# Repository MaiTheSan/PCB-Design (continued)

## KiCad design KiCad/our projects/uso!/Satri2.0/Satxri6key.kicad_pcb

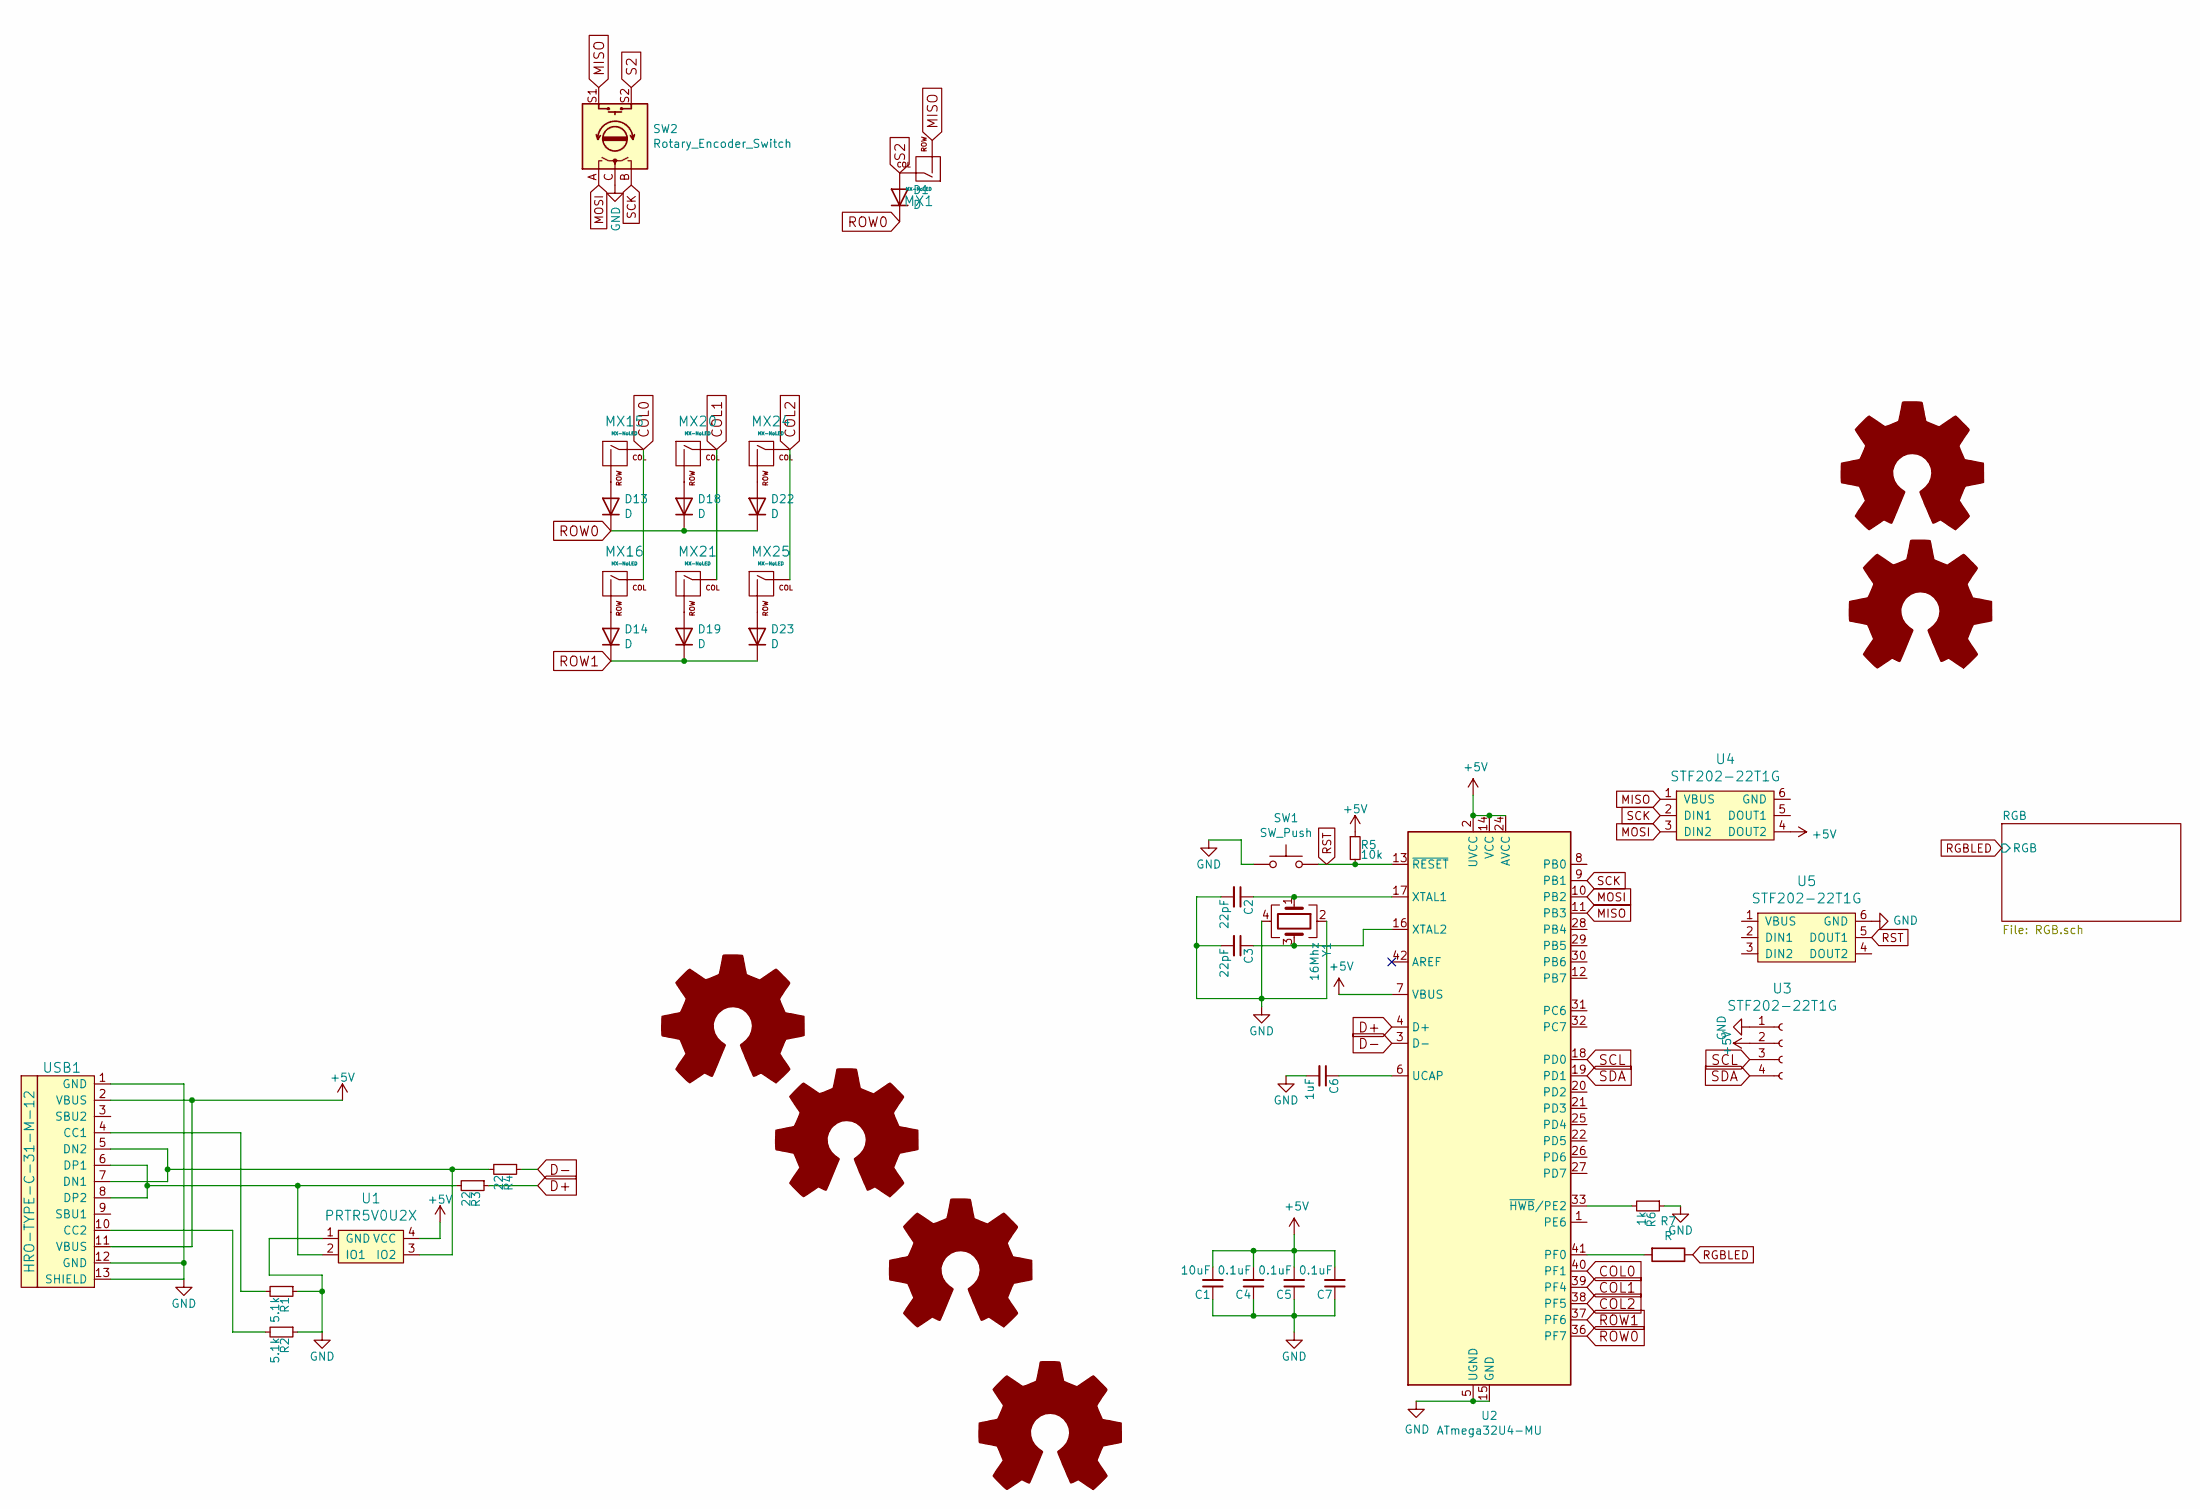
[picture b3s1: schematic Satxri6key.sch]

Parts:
C1: 10uF; C_0603
C2, C3: 22pF; C_0603
C4, C5, C7: 0.1uF; C_0603
C6: 1uF; C_0603
D1, D13, D14, D18, D19, D22, D23: D; D_SOD-123
LOGO1: Logo_Open_Hardware_Large; sanpjxlogo-PCB-type
LOGO2, LOGO3, LOGO4, LOGO5: Logo_Open_Hardware_Large; MountingHole_2.2mm_M2_DIN965_Pad
LOGO6: Logo_Open_Hardware_Large; satxrilogo
MX1, MX15, MX16, MX20, MX21, MX24, MX25: MX-NoLED; MXOnly-1U-Hotswap
R1, R2: 5.1k; R_0805
R3, R4: 22; R_0805
R5: 10k; R_0805
R6: 1k; R_0805
R7: R; R_0805
SW1: SW_Push; SKQG-1155865
SW2: Rotary_Encoder_Switch; RotaryEncoder_Alps_EC11E-Switch_Vertical_H20mm_Center
U1: PRTR5V0U2X; SOT143B
U2: ATmega32U4-MU; QFN-44-1EP_7x7mm_P0.5mm_EP5.2x5.2mm_ThermalVias
U3: STF202-22T1G; 0.91_SSD1306_OLED
U4, U5: STF202-22T1G; Reset_Pretty
USB1: HRO-TYPE-C-31-M-12; HRO-TYPE-C-31-M-12-Assembly
Y1: 16Mhz; Crystal_SMD_3225-4Pin_3.2x2.5mm

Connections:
+5V: C1.2, C4.2, C5.2, C7.2, R5.1, U1.4 (VCC), U2.2 (UVCC), U2.7 (VBUS), U2.14 (VCC), U2.24 (AVCC), U2.34 (VCC), U2.44 (AVCC), U3.2, U4.4 (DOUT2), USB1.2 (VBUS), USB1.11 (VBUS); also elsewhere on the board
COL0: MX15.1 (COL), MX16.1 (COL), U2.40 (PF1)
COL1: MX20.1 (COL), MX21.1 (COL), U2.39 (PF4)
COL2: MX24.1 (COL), MX25.1 (COL), U2.38 (PF5)
D+: R3.1, U2.4 (D+)
D-: R4.1, U2.3 (D-)
GND: C1.1, C2.2, C3.2, C4.1, C5.1, C6.2, C7.1, R1.1, R2.1, R6.1, SW1.1, SW2.C, U1.1 (GND), U2.5 (UGND), U2.15 (GND), U2.23 (GND), U2.35 (GND), U2.43 (GND), U2.45 (GND), U3.1, U5.6 (GND), USB1.1 (GND), USB1.12 (GND), USB1.13 (SHIELD), Y1.2, Y1.4; also elsewhere on the board
MISO: MX1.2 (ROW), SW2.S1, U2.11 (PB3), U4.1 (VBUS)
MOSI: SW2.A, U2.10 (PB2), U4.3 (DIN2)
unnamed: C2.1, U2.17 (XTAL1), Y1.1
unnamed: C3.1, U2.16 (XTAL2), Y1.3
unnamed: C6.1, U2.6 (UCAP)
unnamed: D13.2 (A), MX15.2 (ROW)
unnamed: D14.2 (A), MX16.2 (ROW)
unnamed: D18.2 (A), MX20.2 (ROW)
unnamed: D19.2 (A), MX21.2 (ROW)
unnamed: D22.2 (A), MX24.2 (ROW)
unnamed: D23.2 (A), MX25.2 (ROW)
unnamed: R1.2, USB1.4 (CC1)
unnamed: R2.2, USB1.10 (CC2)
unnamed: R3.2, U1.2 (IO1), USB1.6 (DP1), USB1.8 (DP2)
unnamed: R4.2, U1.3 (IO2), USB1.5 (DN2), USB1.7 (DN1)
unnamed: R6.2, U2.33 (~HWB~/PE2)
unnamed: R7.2, U2.41 (PF0)
RGBLED: R7.1; also elsewhere on the board
ROW0: D1.1 (K), D13.1 (K), D18.1 (K), D22.1 (K), U2.36 (PF7)
ROW1: D14.1 (K), D19.1 (K), D23.1 (K), U2.37 (PF6)
RST: R5.2, SW1.2, U2.13 (~RESET), U5.5 (DOUT1)
S2: D1.2 (A), MX1.1 (COL), SW2.S2
SCK: SW2.B, U2.9 (PB1), U4.2 (DIN1)
SCL: U2.18 (PD0), U3.3
SDA: U2.19 (PD1), U3.4

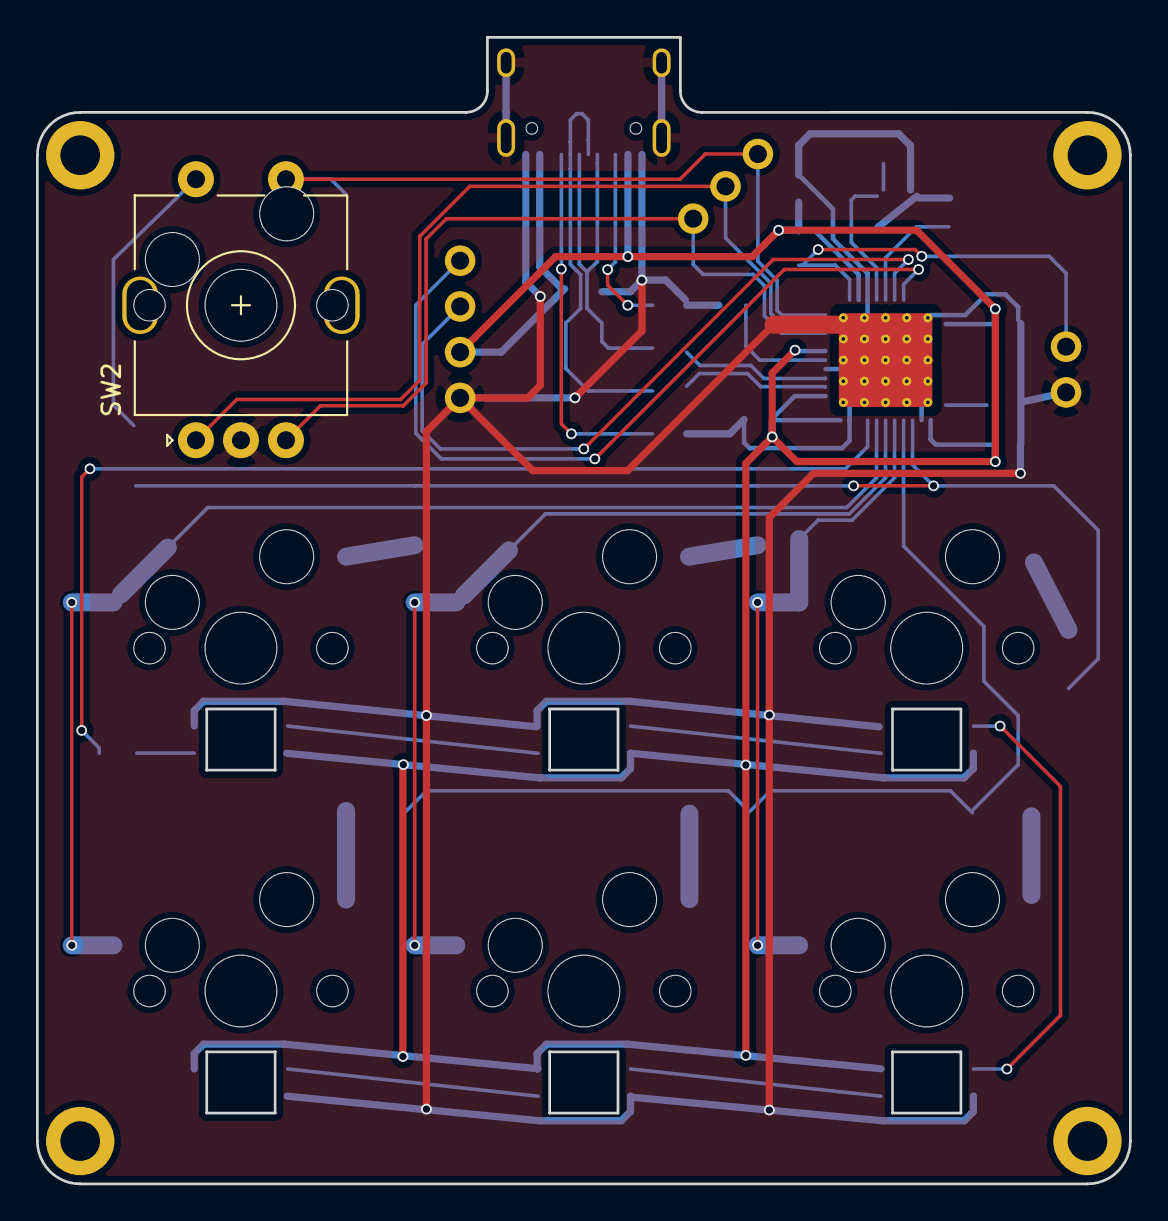
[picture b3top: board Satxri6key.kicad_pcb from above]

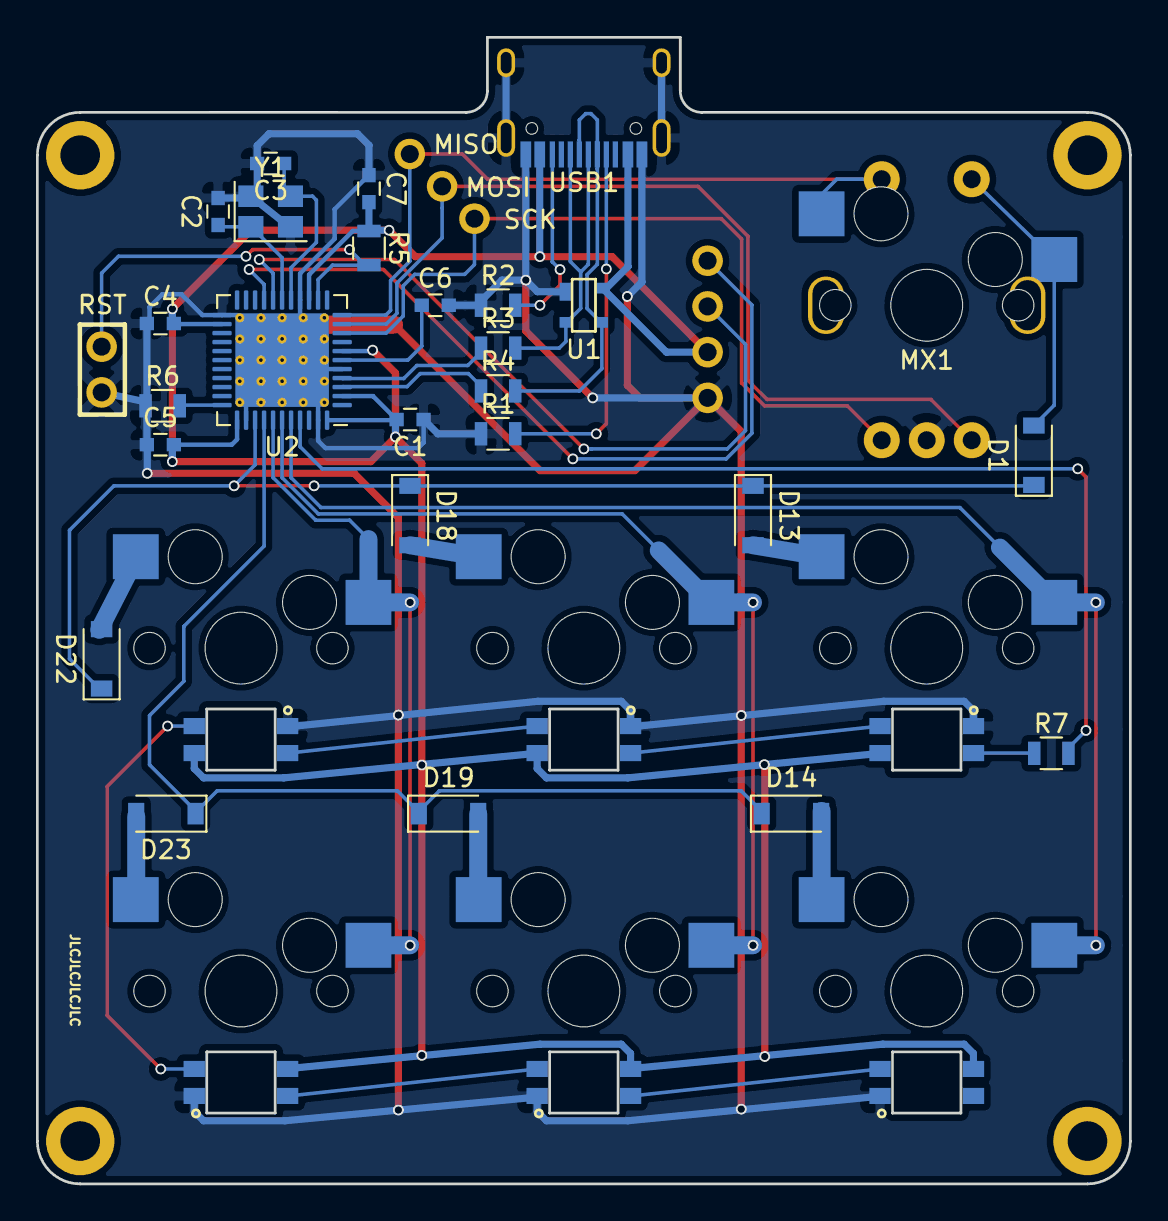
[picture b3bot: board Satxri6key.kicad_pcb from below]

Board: 2 copper layers, 60.7 x 63.7 mm, 46 parts (34 on the bottom side), 37 nets.

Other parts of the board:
SK6812MiniE1, SK6812MiniE2, SK6812MiniE3: WS2812B; RGB-6028_FLIPPED
SK6812MiniE4, SK6812MiniE5, SK6812MiniE6: WS2812B; RGB-6028

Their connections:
+5V: SK6812MiniE1.1, SK6812MiniE2.1, SK6812MiniE3.1, SK6812MiniE4.1, SK6812MiniE5.1, SK6812MiniE6.1; also elsewhere on the board
GND: SK6812MiniE1.3, SK6812MiniE2.3, SK6812MiniE3.3, SK6812MiniE4.3, SK6812MiniE5.3, SK6812MiniE6.3; also elsewhere on the board
unnamed: SK6812MiniE1.2, SK6812MiniE2.4
unnamed: SK6812MiniE2.2, SK6812MiniE3.4
unnamed: SK6812MiniE3.2, SK6812MiniE4.4
unnamed: SK6812MiniE4.2, SK6812MiniE5.4
unnamed: SK6812MiniE5.2, SK6812MiniE6.4
RGBLED: SK6812MiniE1.4; also elsewhere on the board

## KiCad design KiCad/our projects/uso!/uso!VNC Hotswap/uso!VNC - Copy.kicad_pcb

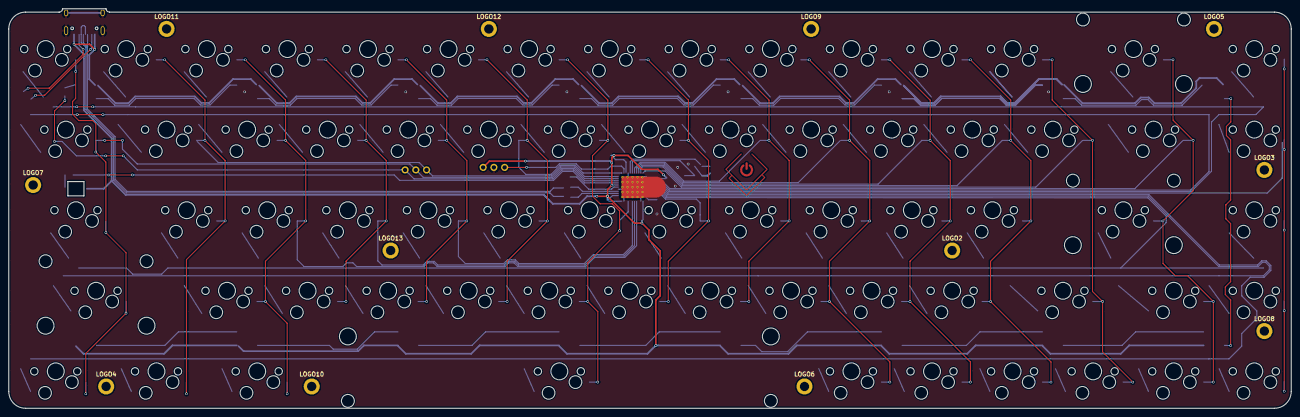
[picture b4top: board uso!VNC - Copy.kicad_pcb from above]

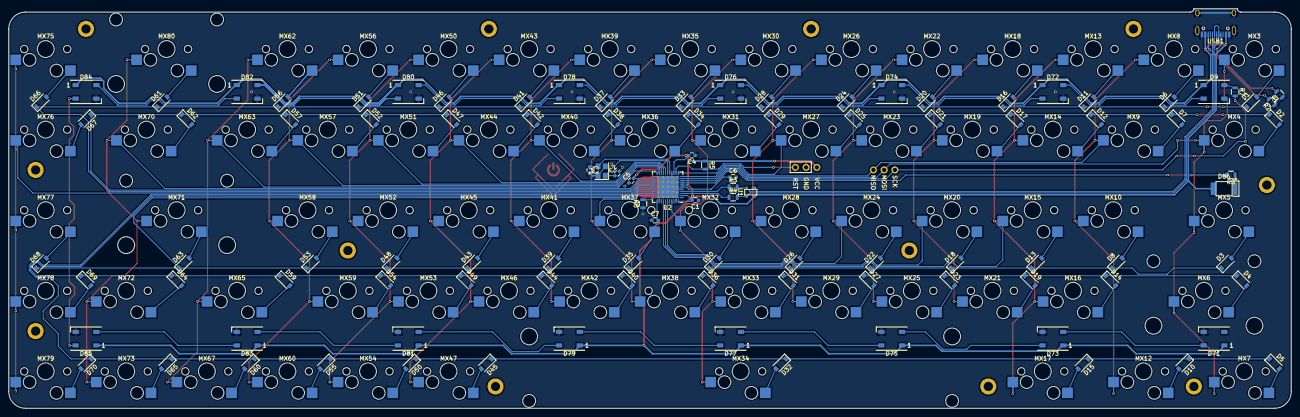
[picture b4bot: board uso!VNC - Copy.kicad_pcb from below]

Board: 2 copper layers, 303.2 x 94.5 mm, 187 parts (105 on the bottom side), 120 nets.

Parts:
C1: 10uF; C_0603
C2, C3: 22pF; C_0603
C4, C5, C7: 0.1uF; C_0603
C6: 1uF; C_0603
D1, D2, D3, D4, D5, D6, D7, D8, D10, D11, D12, D13, D14, D15, D16, D17, D18, D19, D20, D21, D22, D23, D24, D25, D26, D27, D28, D29, D30, D31, D32, D33, D34, D35, D36, D37, D38, D39, D40, D41, D42, D43, D44, D45, D46, D47, D48, D49, D50, D51, D52, D53, D54, D55, D56, D57, D59, D60, D61, D62, D63, D64, D65, D66, D67, D68, D69, D70: D; D_SOD-123
D9, D71, D72, D73, D74, D75, D76, D77, D78, D79, D80, D81, D82, D83, D84, D85: WS2812B; LED_WS2812B_PLCC4_5.0x5.0mm_P3.2mm
D86: LED; LED-6028
LOGO1: Logo_Open_Hardware_Large; sanpjxlogo-PCB-type
LOGO2, LOGO3, LOGO4, LOGO5, LOGO6, LOGO7, LOGO8, LOGO9, LOGO10, LOGO11, LOGO12, LOGO13: Logo_Open_Hardware_Large; MountingHole_2.2mm_M2_DIN965_Pad
MX3, MX8, MX9, MX10, MX13, MX14, MX15, MX16, MX18, MX19, MX20, MX21, MX22, MX23, MX24, MX25, MX26, MX27, MX28, MX29, MX30, MX31, MX32, MX33, MX35, MX36, MX37, MX38, MX39, MX40, MX41, MX42, MX43, MX44, MX45, MX46, MX47, MX50, MX51, MX52, MX53, MX54, MX56, MX57, MX58, MX59, MX60, MX62, MX63, MX67, MX72, MX73, MX75, MX76, MX77, MX78, MX79: MX-NoLED; MXOnly-1U-Hotswap
MX4, MX70: MX-NoLED; MXOnly-1.5U-Hotswap
MX5: MX-.75; MXOnly-1.75U-Hotswap
MX6: MX-2.25; MXOnly-2.25U-Hotswap-ReversedStabilizers
MX7, MX12, MX17: MX-1.25; MXOnly-1.25U-Hotswap
MX34: MX-6.25; MXOnly-6.25U-Hotswap
MX65: MX-NoLED; MXOnly-1.75U-Hotswap
MX71: MX-NoLED; MXOnly-2.25U-Hotswap-ReversedStabilizers
MX80: MX-NoLED; MXOnly-2U-Hotswap-ReversedStabilizers
R1, R2: 5.1k; R_0805
R3, R4: 22; R_0805
R5: 10k; R_0805
R6: 1k; R_0805
R7, R8: R; R_0805
U1: PRTR5V0U2X; SOT143B
U2: ATmega32U4-MU; QFN-44-1EP_7x7mm_P0.5mm_EP5.2x5.2mm_ThermalVias
U3, U4: STF202-22T1G; Reset_Pretty
USB1: HRO-TYPE-C-31-M-12; HRO-TYPE-C-31-M-12-Assembly
Y1: 16Mhz; Crystal_SMD_3225-4Pin_3.2x2.5mm

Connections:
+5V: C1.2, C4.2, C5.2, C7.2, D9.1, D71.1, D72.1, D73.1, D74.1, D75.1, D76.1, D77.1, D78.1, D79.1, D80.1, D81.1, D82.1, D83.1, D84.1, D85.1, D86.2, R5.1, U1.4, U2.2, U2.7, U2.14, U2.24, U2.34, U2.44, U4.2, USB1.2, USB1.11
COL2: MX13.1, MX14.1, MX15.1, MX16.1, MX17.1, U2.37
COL3: MX18.1, MX19.1, MX20.1, MX21.1, U2.38
COL4: MX22.1, MX23.1, MX24.1, MX25.1, U2.39
COL5: MX26.1, MX27.1, MX28.1, MX29.1, U2.12
COL6: MX30.1, MX31.1, MX32.1, MX33.1, MX34.1, U2.41
COL7: MX35.1, MX36.1, MX37.1, MX38.1, U2.32
COL8: MX39.1, MX40.1, MX41.1, MX42.1, U2.18
COL9: MX43.1, MX44.1, MX45.1, MX46.1, MX47.1, U2.19
COL10: MX50.1, MX51.1, MX52.1, MX53.1, MX54.1, U2.20
COL11: MX56.1, MX57.1, MX58.1, MX59.1, MX60.1, U2.21
COL12: MX62.1, MX63.1, MX65.1, MX67.1, U2.22
COL13: MX70.1, MX71.1, MX72.1, MX73.1, MX80.1, U2.25
COL14: MX75.1, MX76.1, MX77.1, MX78.1, MX79.1, U2.28
CapS: R8.2, U2.8
D+: R3.1, U2.4
D-: R4.1, U2.3
GND: C1.1, C2.2, C3.2, C4.1, C5.1, C6.2, C7.1, D9.3, D71.3, D72.3, D73.3, D74.3, D75.3, D76.3, D77.3, D78.3, D79.3, D80.3, D81.3, D82.3, D83.3, D84.3, D85.3, R1.1, R2.1, R6.1, U1.1, U2.5, U2.15, U2.23, U2.35, U2.43, U2.45, U4.6, USB1.1, USB1.12, USB1.13, Y1.2, Y1.4
MISO: MX8.1, MX9.1, MX10.1, MX12.1, U2.11, U3.1
MOSI: MX3.1, MX4.1, MX5.1, MX6.1, MX7.1, U2.10, U3.4
unnamed: C2.1, U2.17, Y1.1
unnamed: C3.1, U2.16, Y1.3
unnamed: C6.1, U2.6
unnamed: D1.2, MX3.2
unnamed: D2.2, MX4.2
unnamed: D3.2, MX5.2
unnamed: D4.2, MX6.2
unnamed: D5.2, MX7.2
unnamed: D6.2, MX8.2
unnamed: D7.2, MX9.2
unnamed: D8.2, MX10.2
unnamed: D9.4, R7.1
unnamed: D10.2, MX12.2
unnamed: D11.2, MX13.2
unnamed: D12.2, MX14.2
unnamed: D13.2, MX15.2
unnamed: D14.2, MX16.2
unnamed: D15.2, MX17.2
unnamed: D16.2, MX18.2
unnamed: D17.2, MX19.2
unnamed: D18.2, MX20.2
unnamed: D19.2, MX21.2
unnamed: D20.2, MX22.2
unnamed: D21.2, MX23.2
unnamed: D22.2, MX24.2
unnamed: D23.2, MX25.2
unnamed: D24.2, MX26.2
unnamed: D25.2, MX27.2
unnamed: D26.2, MX28.2
unnamed: D27.2, MX29.2
unnamed: D28.2, MX30.2
unnamed: D29.2, MX31.2
unnamed: D30.2, MX32.2
unnamed: D31.2, MX33.2
unnamed: D32.2, MX34.2
unnamed: D33.2, MX35.2
unnamed: D34.2, MX36.2
unnamed: D35.2, MX37.2
unnamed: D36.2, MX38.2
unnamed: D37.2, MX39.2
unnamed: D38.2, MX40.2
unnamed: D39.2, MX41.2
unnamed: D40.2, MX42.2
unnamed: D41.2, MX43.2
unnamed: D42.2, MX44.2
unnamed: D43.2, MX45.2
unnamed: D44.2, MX46.2
unnamed: D45.2, MX47.2
unnamed: D46.2, MX50.2
unnamed: D47.2, MX51.2
unnamed: D48.2, MX52.2
unnamed: D49.2, MX53.2
unnamed: D50.2, MX54.2
unnamed: D51.2, MX56.2
unnamed: D52.2, MX57.2
unnamed: D53.2, MX58.2
unnamed: D54.2, MX59.2
unnamed: D55.2, MX60.2
unnamed: D56.2, MX62.2
unnamed: D57.2, MX63.2
unnamed: D59.2, MX65.2
unnamed: D60.2, MX67.2
unnamed: D61.2, MX80.2
unnamed: D62.2, MX70.2
unnamed: D63.2, MX71.2
unnamed: D64.2, MX72.2
unnamed: D65.2, MX73.2
unnamed: D66.2, MX75.2
unnamed: D67.2, MX76.2
unnamed: D68.2, MX77.2
unnamed: D69.2, MX78.2
unnamed: D70.2, MX79.2
unnamed: D71.4, D73.2
unnamed: D72.2, D74.4
unnamed: D9.2, D72.4
unnamed: D73.4, D75.2
unnamed: D74.2, D76.4
unnamed: D75.4, D77.2
unnamed: D76.2, D78.4
unnamed: D77.4, D79.2
unnamed: D78.2, D80.4
unnamed: D79.4, D81.2
unnamed: D80.2, D82.4
unnamed: D81.4, D83.2
unnamed: D82.2, D84.4
unnamed: D83.4, D85.2
unnamed: D84.2, D85.4
unnamed: D86.1, R8.1
unnamed: R1.2, USB1.4
unnamed: R2.2, USB1.10
unnamed: R3.2, U1.2, USB1.6, USB1.8
unnamed: R4.2, U1.3, USB1.5, USB1.7
unnamed: R6.2, U2.33
ROW0: D1.1, D6.1, D11.1, D16.1, D20.1, D24.1, D28.1, D33.1, D37.1, D41.1, D46.1, D51.1, D56.1, D61.1, D66.1, U2.27
ROW1: D2.1, D7.1, D12.1, D17.1, D21.1, D25.1, D29.1, D34.1, D38.1, D42.1, D47.1, D52.1, D57.1, D62.1, D67.1, U2.26
ROW2: D3.1, D8.1, D13.1, D18.1, D22.1, D26.1, D30.1, D35.1, D39.1, D43.1, D48.1, D53.1, D63.1, D68.1, U2.31
ROW3: D4.1, D14.1, D19.1, D23.1, D27.1, D31.1, D36.1, D40.1, D44.1, D49.1, D54.1, D59.1, D64.1, D69.1, U2.30
ROW4: D5.1, D10.1, D15.1, D32.1, D45.1, D50.1, D55.1, D60.1, D65.1, D70.1, U2.29
RST: R5.2, U2.13, U4.5
SCK: R7.2, U2.9, U3.3
